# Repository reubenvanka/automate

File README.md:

# Auto Mate

Auto Mate is the working product repository for a smart-room controller. The current confirmed intent is coordinated control of lighting and fans, including brightness and color-temperature control, environmental sensing, Home Assistant integration, and a local/custom web interface.

## Current status

This repository contains the product foundation only. No GPIO assignments, controller model, electrical schematic, PCB, enclosure, or production safety decisions have been approved yet.

## Repository boundaries

- `SPECIFICATIONS.md` — source of truth.
- `firmware/esphome/` — future ESPHome product configuration and modules.
- `hardware/kicad/` — future KiCad projects and review artifacts.
- `tests/` — firmware, integration, UX, and hardware-review evidence.
- `docs/` — architecture, AI context, gates, traceability, and release evidence.
- `releases/` — approved release notes and artifacts.
- `backups/` — local working backups; not public release artifacts.

## Safety and review boundary

AI may prepare candidate firmware, schematics, netlists, PCB outlines, placement, and validation reports. A human must approve final GPIO mappings, electrical connections, component choices, load switching, placement, routing, safety behavior, and release.

## Security

Never commit Wi-Fi credentials, Home Assistant tokens, API keys, customer data, or private commercial information. Keep secrets outside Git and use documented configuration templates.

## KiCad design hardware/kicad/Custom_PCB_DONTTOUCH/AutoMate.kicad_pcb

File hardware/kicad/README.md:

# Auto Mate KiCad Hardware

This directory is reserved for KiCad projects, symbol/footprint libraries, netlists, ERC/DRC reports, and human review artifacts.

No schematic or PCB is manufacturing-ready until the hardware architecture is approved and the required human review is recorded.

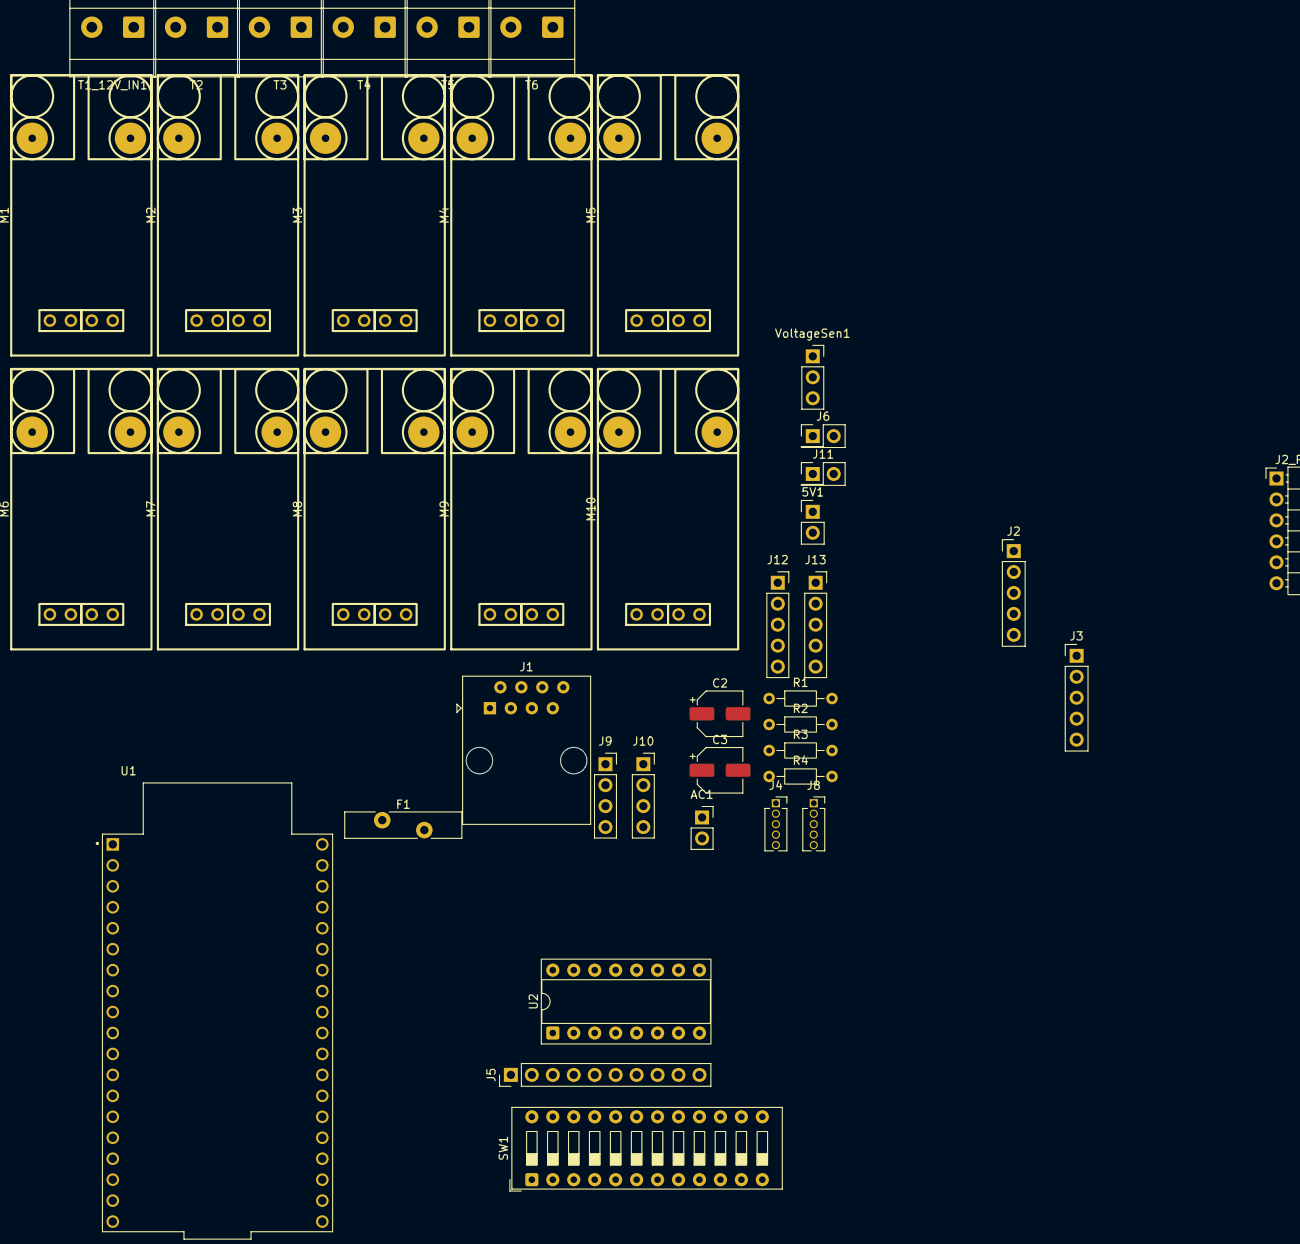
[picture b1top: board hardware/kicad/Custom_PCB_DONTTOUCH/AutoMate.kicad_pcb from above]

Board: 8 copper layers, 42 parts (0 on the bottom side), 24 nets, no tracks yet.

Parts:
5V1: GND; PinHeader_1x02_P2.54mm_Vertical
AC1: PinSocket_1x02_P2.54mm_Vertical
C2: 100nF; CP_Elec_5x3.9
C3: 470uf; CP_Elec_5x3.9
F1: Polyfuse; Fuse_Bourns_MF-RHT700
J1: 8P8C; RJ45_Amphenol_54602-x08_Horizontal
J2: SDA; PinHeader_1x05_P2.54mm_Vertical
J2_PCA9685: PCA9685; PinHeader_1x06_P2.54mm_Horizontal
J3: SCL; PinHeader_1x05_P2.54mm_Vertical
J4: +5V; PinSocket_1x05_P1.27mm_Vertical
J5: Relay; PinHeader_1x10_P2.54mm_Vertical
J6: tx rx; PinHeader_2x01_P2.54mm_Vertical
J8: GND; PinSocket_1x05_P1.27mm_Vertical
J9: ZMPT; PinSocket_1x04_P2.54mm_Vertical
J10: Sensors all; PinSocket_1x04_P2.54mm_Vertical
J11: Door Sensor; PinHeader_2x01_P2.54mm_Vertical
J12: a; PinSocket_1x05_P2.54mm_Vertical
J13: Rst-boot-led-ws2812b-3.3v; PinSocket_1x05_P2.54mm_Vertical
M1, M2, M3, M4, M5, M6, M7, M8, M9, M10: D4184 Module Custom Updated
R1, R3: 4.7k Pull-up SDA/SCL; R_Axial_DIN0204_L3.6mm_D1.6mm_P7.62mm_Horizontal
R2: 1k Ohm; R_Axial_DIN0204_L3.6mm_D1.6mm_P7.62mm_Horizontal
R4: 10k Pull-Down; R_Axial_DIN0204_L3.6mm_D1.6mm_P7.62mm_Horizontal
SW1: SW_DIP_x12; SW_DIP_SPSTx12_Slide_9.78x32.66mm_W7.62mm_P2.54mm
T1_12V_IN1, T2, T3, T4, T5, T6: Screw_Terminal_01x02; TerminalBlock_Phoenix_MKDS-3-2-5.08_1x02_P5.08mm_Horizontal
U1: ESP32-DEVKITC; MODULE_ESP32-DEVKITC
U2: 74HC595; DIP-16_W7.62mm_Socket
VoltageSen1: PinSocket_1x03_P2.54mm_Vertical

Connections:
04 PWM/Relay-WS2812b: J1.3, J13.2, R4.1
16 PWM/Relay/rx2: J1.6, J6.2, R2.2
17 PWM/Relay/tx2: J1.5, J6.1
21 SDA: J1.1, J2.1, J2.2, J2.3, J2.4, J2.5, R3.1
22 SCL: J1.8, J3.1, J3.2, J3.3, J3.4, J3.5, R1.1
34 IP_ONLY: J9.2, J10.3
35 IP_ONLY: J10.4, VoltageSen1.2
36 IP_ONLY: J10.1, J11.2
+3.3V: J1.7, J13.1, U1.1 (3V3)
+5V: AC1.1, C2.2, C3.2, F1.1, J1.4, J4.1, J4.2, J4.3, J4.4, J4.5, J5.10, J9.1, R1.2, R3.2, R4.2, VoltageSen1.1
GND: 5V1.2 (-), AC1.2, C2.1, C3.1, J1.2, J2_PCA9685.1, J5.1, J8.1, J8.2, J8.3, J8.4, J8.5, J9.3, J9.4, J11.1, J12.5, M1.4 (GND), M2.4 (GND), M3.4 (GND_4), M4.4 (GND_4), M5.4 (GND_4), M6.4 (GND_4), M7.4 (GND_4), M8.4 (GND_4), M9.4 (GND_4), M10.4 (GND_4), U1.38 (GND3), VoltageSen1.3
unnamed: 5V1.1 (+), F1.2
unnamed: J5.2, SW1.24, U2.15 (QA)
unnamed: J5.3, SW1.23, U2.1 (QB)
unnamed: J5.4, SW1.22, U2.2 (QC)
unnamed: J5.5, SW1.21, U2.3 (QD)
unnamed: J5.6, SW1.20, U2.4 (QE)
unnamed: J5.7, SW1.19, U2.5 (QF)
unnamed: J5.8, SW1.18, U2.6 (QG)
unnamed: J5.9, SW1.17, U2.7 (QH)
unnamed: SW1.1, SW1.2, SW1.3, SW1.4, SW1.5, SW1.6, SW1.7, SW1.8, SW1.9, SW1.10, SW1.11, SW1.12
PCA9685_OE (with 10kΩ pull-up to 3.3V): J2_PCA9685.2, U1.25 (IO0)
PWM_CEILING_COLD: M2.1 (PWM), U1.34 (RXD0)
PWM_CEILING_WARM: M1.1 (PWM), U1.35 (TXD0)

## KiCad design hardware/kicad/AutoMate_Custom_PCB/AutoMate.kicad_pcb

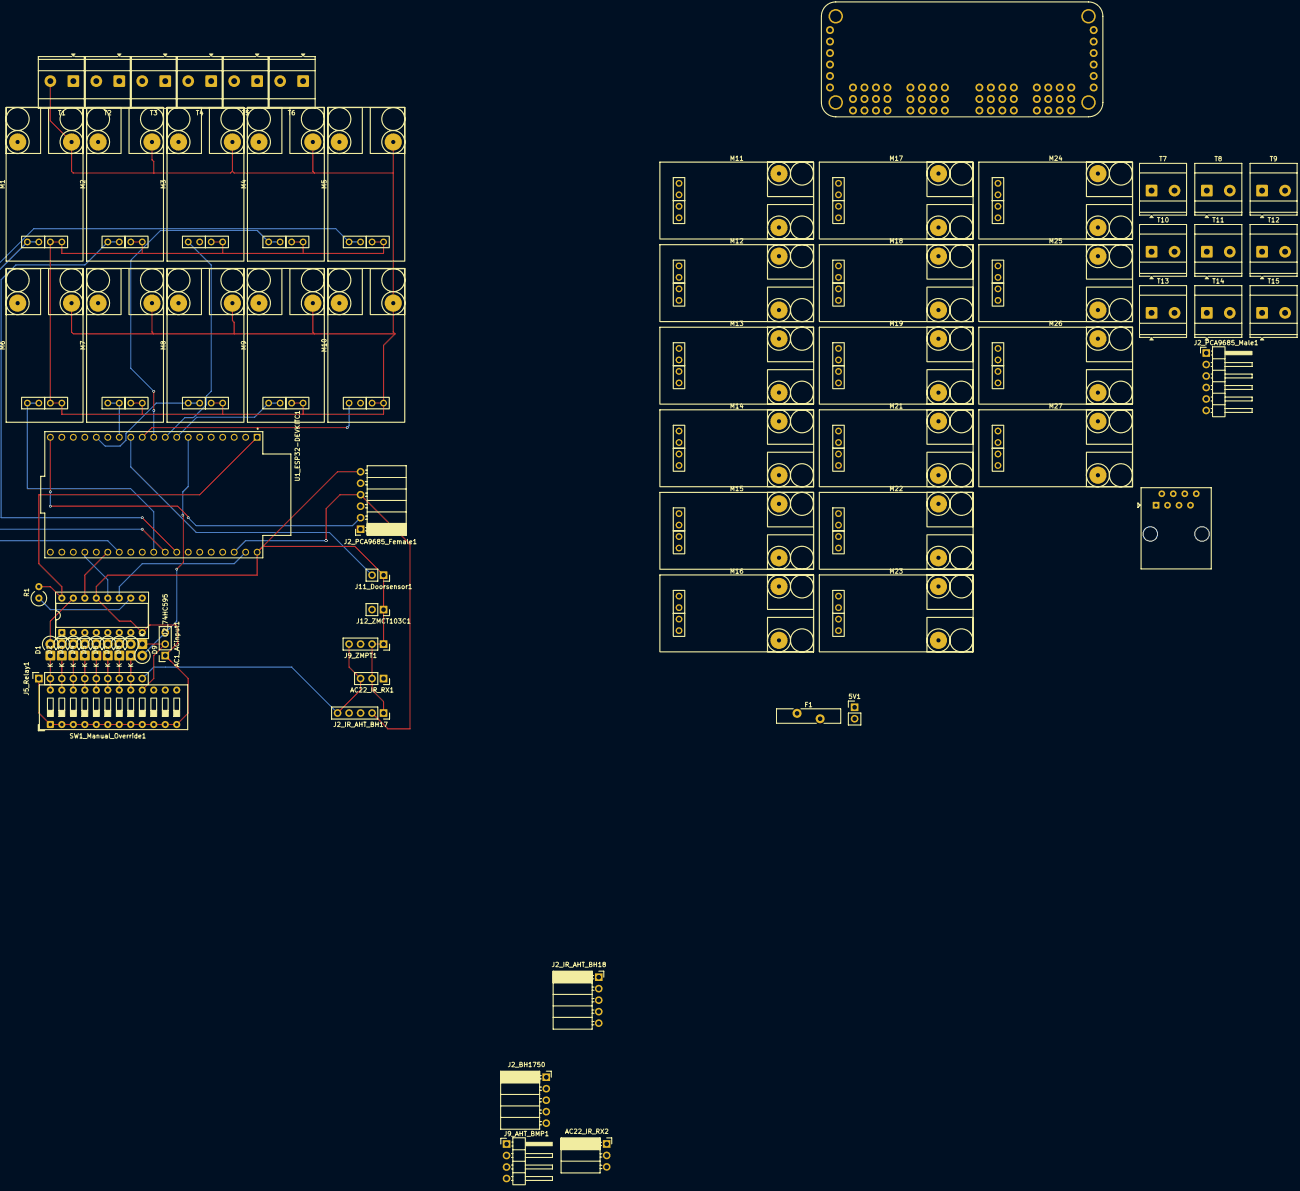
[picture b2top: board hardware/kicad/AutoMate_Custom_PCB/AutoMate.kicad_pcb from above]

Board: 8 copper layers, 71 parts (0 on the bottom side), 85 nets.

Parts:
5V1: GND; PinHeader_1x02_P2.54mm_Vertical
AC1_ACinput1, AC22_IR_RX1: Conn_01x03_Socket; PinSocket_1x03_P2.54mm_Vertical
AC22_IR_RX2: Conn_01x03_Socket; PinSocket_1x03_P2.54mm_Horizontal
D1, D2, D3, D4, D5, D6, D7, D8, D9: 1N5817; D_DO-41_SOD81_P2.54mm_Vertical_CathodeUp
F1: Polyfuse; Fuse_Bourns_MF-RHT700
J1: 8P8C; RJ45_Amphenol_54602-x08_Horizontal
J2_BH1750, J2_IR_AHT_BH18: Conn_01x05_Socket; PinSocket_1x05_P2.54mm_Horizontal
J2_IR_AHT_BH17: Conn_01x05_Socket; PinSocket_1x05_P2.54mm_Vertical
J2_PCA9685_Female1: PCA9685; PinSocket_1x06_P2.54mm_Horizontal
J2_PCA9685_Male1: PCA9685; PinHeader_1x06_P2.54mm_Horizontal
J5_Relay1: Relay; PinSocket_1x10_P2.54mm_Vertical
J9_AHT_BMP1: Conn_01x04_Socket; PinHeader_1x04_P2.54mm_Horizontal
J9_ZMPT1: Conn_01x04_Socket; PinSocket_1x04_P2.54mm_Vertical
J11_Doorsensor1, J12_ZMCT103C1: Conn_01x02_Socket; PinSocket_1x02_P2.54mm_Vertical
M1, M2, M3, M4, M5, M6, M7, M8, M9, M10, M11, M12, M13, M14, M15, M16, M17, M18, M19, M21, M22, M23, M24, M25, M26, M27: D4184 Module Custom Updated
R1: 10k; R_Axial_DIN0309_L9.0mm_D3.2mm_P2.54mm_Vertical
SW1_Manual_Override1: SW_DIP_x12; SW_DIP_SPSTx12_Slide_9.78x32.66mm_W7.62mm_P2.54mm
T1, T2, T3, T4, T5, T6, T7: Screw_Terminal_01x02; TerminalBlock_Phoenix_MKDS-3-2-5.08_1x02_P5.08mm_Horizontal
T8, T9, T10, T11, T12, T13, T14, T15: ST01x02; TerminalBlock_Phoenix_MKDS-3-2-5.08_1x02_P5.08mm_Horizontal
U1: 815; MODULE_815_pca9685
U1_ESP32-DEVKITC1: ESP32-DEVKITC; MODULE_ESP32-DEVKITC
U2_74HC595: 74HC595; DIP-16_W7.62mm_Socket

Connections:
30A_JN: AC1_ACinput1.3, D9.1, SW1_Manual_Override1.16
+3.3V: J1.7, R1.2, U1_ESP32-DEVKITC1.1 (3V3), U2_74HC595.16 (VCC)
+5V: AC1_ACinput1.1, AC22_IR_RX1.3, AC22_IR_RX2.3, F1.1, J1.4, J2_BH1750.5, J2_IR_AHT_BH17.5, J2_IR_AHT_BH18.5, J2_PCA9685_Female1.2, J2_PCA9685_Male1.5, J5_Relay1.10, J9_AHT_BMP1.1, J9_ZMPT1.4, U1.VCC_1 (VCC), U1.VCC_2 (VCC), U1_ESP32-DEVKITC1.19 (EXT_5V)
+12V: T1.1, T7.1
BACKUP_01: M26.1 (PWM), M26.2 (PWM), U1.14 (PWM_14)
BACKUP_02: M27.1 (PWM), M27.2 (PWM), U1.15 (PWM_15)
BU1: M26.5 (Led), T15.1
BU2: M27.5 (Led), T15.2
CBL: M18.5 (Led), T11.2
CC: M2.5 (Led), T2.2
CEILING_COLD: M2.1 (PWM), M2.2 (PWM), U1_ESP32-DEVKITC1.31 (IO19)
CEILING_WARM: M1.1 (PWM), M1.2 (PWM), U1_ESP32-DEVKITC1.30 (IO18)
CSL: M19.5 (Led), T12.1
CUPBOARD_BOUNCE_LIGHT: M18.1 (PWM), M18.2 (PWM), U1.7 (PWM_7)
CUPBOARD_SPOT_LIGHT: M19.1 (PWM), M19.2 (PWM), U1.8 (PWM_8)
CW: M1.5 (Led), T2.1
D1C: M4.5 (Led), T3.2
D1W: M3.5 (Led), T3.1
D2C: M6.5 (Led), T4.2
D2W: M5.5 (Led), T4.1
DESK1_COLD: M4.1 (PWM), M4.2 (PWM), U1_ESP32-DEVKITC1.10 (IO26)
DESK1_WARM: M3.1 (PWM), M3.2 (PWM), U1_ESP32-DEVKITC1.9 (IO25)
DESK2_COLD: M6.1 (PWM), M6.2 (PWM), U1_ESP32-DEVKITC1.29 (IO5)
DESK2_WARM: M5.1 (PWM), M5.2 (PWM), U1_ESP32-DEVKITC1.26 (IO4)
DESK_LIGHT1: M12.1 (PWM), M12.2 (PWM), U1.1 (PWM_1)
DESK_LIGHT2: M16.1 (PWM), M16.2 (PWM), U1.5 (PWM_5)
DL1: M12.5 (Led), T8.2
DL2: M16.5 (Led), T10.2
DOOR_SENSOR: J11_Doorsensor1.2, U1_ESP32-DEVKITC1.12 (IO14)
DOOR_SPOT_LIGHT: M21.1 (PWM), M21.2 (PWM), U1.9 (PWM_9)
DSL: M21.5 (Led), T12.2
EF: M24.5 (Led), T14.1
EXHAUST_FANS: M24.1 (PWM), M24.2 (PWM), U1.12 (PWM_12)
GND: 5V1.2 (-), AC1_ACinput1.2, AC22_IR_RX1.2, AC22_IR_RX2.2, J1.2, J2_BH1750.1, J2_IR_AHT_BH17.1, J2_IR_AHT_BH18.1, J2_PCA9685_Female1.6, J2_PCA9685_Male1.1, J5_Relay1.1, J9_AHT_BMP1.3, J9_ZMPT1.1, J9_ZMPT1.2, J11_Doorsensor1.1, J12_ZMCT103C1.1, M1.3 (GND), M1.4 (GND), M1.6 (Gnd), M2.3 (GND), M2.4 (GND), M2.6 (Gnd), M3.3 (GND), M3.4 (GND), M3.6 (Gnd), M4.3 (GND), M4.4 (GND), M4.6 (Gnd), M5.3 (GND), M5.4 (GND), M5.6 (Gnd), M6.3 (GND), M6.4 (GND), M6.6 (Gnd), M7.3 (GND), M7.4 (GND), M7.6 (Gnd), M8.3 (GND), M8.4 (GND), M8.6 (Gnd), M9.3 (GND), M9.4 (GND), M9.6 (Gnd), M10.3 (GND), M10.4 (GND), M10.6 (Gnd), M11.3 (GND), M11.4 (GND), M11.6 (Gnd), M12.3 (GND), M12.4 (GND), M12.6 (Gnd), M13.3 (GND), M13.4 (GND), M13.6 (Gnd), M14.3 (GND), M14.4 (GND), M14.6 (Gnd), M15.3 (GND), M15.4 (GND), M15.6 (Gnd), M16.3 (GND), M16.4 (GND), M16.6 (Gnd), M17.3 (GND), M17.4 (GND), M17.6 (Gnd), M18.3 (GND), M18.4 (GND), M18.6 (Gnd), M19.3 (GND), M19.4 (GND), M19.6 (Gnd), M21.3 (GND), M21.4 (GND), M21.6 (Gnd), M22.3 (GND), M22.4 (GND), M22.6 (Gnd), M23.3 (GND), M23.4 (GND), M23.6 (Gnd), M24.3 (GND), M24.4 (GND), M24.6 (Gnd), M25.3 (GND), M25.4 (GND), M25.6 (Gnd), M26.3 (GND), M26.4 (GND), M26.6 (Gnd), M27.3 (GND), M27.4 (GND), M27.6 (Gnd), SW1_Manual_Override1.1, SW1_Manual_Override1.2, SW1_Manual_Override1.3, SW1_Manual_Override1.4, SW1_Manual_Override1.5, SW1_Manual_Override1.6, SW1_Manual_Override1.7, SW1_Manual_Override1.8, SW1_Manual_Override1.9, SW1_Manual_Override1.10, SW1_Manual_Override1.11, SW1_Manual_Override1.12, T1.2, T7.2, U1.GND_1 (GND), U1.GND_2 (GND), U1.GND_3 (GND), U1.GND_4 (GND), U1.GND_5 (GND), U1.GND_6 (GND), U1.GND_7 (GND), U1.GND_8 (GND), U1.GND_9 (GND), U1.GND_10 (GND), U1.GND_11 (GND), U1.GND_12 (GND), U1.GND_13 (GND), U1.GND_14 (GND), U1.GND_15 (GND), U1.GND_16 (GND), U1.GND_17 (GND), U1.GND_18 (GND), U1_ESP32-DEVKITC1.38 (GND3), U2_74HC595.8 (GND), U2_74HC595.13 (~OE)
I2C_SCL: J2_BH1750.4, J2_IR_AHT_BH17.2, J2_IR_AHT_BH18.2, J2_PCA9685_Female1.4, J2_PCA9685_Male1.3, J9_AHT_BMP1.4, U1.SCL_1 (SCL), U1.SCL_2 (SCL), U1_ESP32-DEVKITC1.36 (IO22)
I2C_SDA: J2_BH1750.3, J2_IR_AHT_BH17.3, J2_IR_AHT_BH18.3, J2_PCA9685_Female1.3, J2_PCA9685_Male1.4, J9_AHT_BMP1.2, U1.SDA_1 (SDA), U1.SDA_2 (SDA), U1_ESP32-DEVKITC1.33 (IO21)
IR_RX: AC22_IR_RX1.1, AC22_IR_RX2.1, J2_IR_AHT_BH17.4, J2_IR_AHT_BH18.4, U1_ESP32-DEVKITC1.4 (SENSOR_VN)
M1B: M11.5 (Led), T8.1
M2B: M15.5 (Led), T10.1
M3B: M22.5 (Led), T13.1
M4B: M23.5 (Led), T13.2
MONITOR1_BACKLIGHT: M11.1 (PWM), M11.2 (PWM), U1.0 (PWM_0)
MONITOR2_BACKLIGHT: M15.1 (PWM), M15.2 (PWM), U1.4 (PWM_4)
MONITOR3_BACKLIGHT: M22.1 (PWM), M22.2 (PWM), U1.10 (PWM_10)
MONITOR4_BACKLIGHT: M23.1 (PWM), M23.2 (PWM), U1.11 (PWM_11)
unnamed: 5V1.1 (+), F1.2
unnamed: D1.1, J5_Relay1.2, SW1_Manual_Override1.24
unnamed: D2.1, J5_Relay1.3, SW1_Manual_Override1.23
unnamed: D3.1, J5_Relay1.4, SW1_Manual_Override1.22
unnamed: D4.1, J5_Relay1.5, SW1_Manual_Override1.21
unnamed: D5.1, J5_Relay1.6, SW1_Manual_Override1.20
unnamed: D6.1, J5_Relay1.7, SW1_Manual_Override1.19
unnamed: D7.1, J5_Relay1.8, SW1_Manual_Override1.18
unnamed: D8.1, J5_Relay1.9, SW1_Manual_Override1.17
unnamed: D1.2, U2_74HC595.15 (QA)
unnamed: D2.2, U2_74HC595.1 (QB)
unnamed: D3.2, U2_74HC595.2 (QC)
unnamed: D4.2, U2_74HC595.3 (QD)
unnamed: D5.2, U2_74HC595.4 (QE)
unnamed: D6.2, U2_74HC595.5 (QF)
unnamed: D7.2, U2_74HC595.6 (QG)
unnamed: D8.2, U2_74HC595.7 (QH)
unnamed: R1.1, U2_74HC595.10 (~SRCLR)
PHOTO_SPOT_LIGHT: M7.1 (PWM), M7.2 (PWM), U1_ESP32-DEVKITC1.13 (IO12)
PSL: M8.5 (Led), T5.2
RCLK: U1_ESP32-DEVKITC1.23 (IO15), U2_74HC595.12 (RCLK)
RELAY_30A: D9.2, U1_ESP32-DEVKITC1.7 (IO32)
SER: U1_ESP32-DEVKITC1.25 (IO0), U2_74HC595.14 (SER)
SHELF_LIGHT1: M14.1 (PWM), M14.2 (PWM), U1.3 (PWM_3)
SHELF_LIGHT2: M17.1 (PWM), M17.2 (PWM), U1.6 (PWM_6)
SHL1: M14.5 (Led), T9.2
SHL2: M17.5 (Led), T11.1
SRCLK: U1_ESP32-DEVKITC1.37 (IO23), U2_74HC595.11 (SRCLK)
TABLE_LIGHT: M13.1 (PWM), M13.2 (PWM), U1.2 (PWM_2)
TAL: M25.5 (Led), T14.2
TBLL: M13.5 (Led), T9.1
TERRACE_AMBIENT_LIGHT: M25.1 (PWM), M25.2 (PWM), U1.13 (PWM_13)
TERRACE_LIGHT: M10.1 (PWM), M10.2 (PWM), U1_ESP32-DEVKITC1.11 (IO27)
TL: M10.5 (Led), T6.2
WALL_BOUNCE_LIGHT: M8.1 (PWM), M8.2 (PWM), U1_ESP32-DEVKITC1.15 (IO13)
WASHROOM_LIGHT: M9.1 (PWM), M9.2 (PWM), U1_ESP32-DEVKITC1.8 (IO33)
WBL: M7.5 (Led), T5.1
WL: M9.5 (Led), T6.1
ZMCT103C_CURRENT: J12_ZMCT103C1.2, U1_ESP32-DEVKITC1.5 (IO34)
ZMPT101B_VOLTAGE: J9_ZMPT1.3, U1_ESP32-DEVKITC1.6 (IO35)

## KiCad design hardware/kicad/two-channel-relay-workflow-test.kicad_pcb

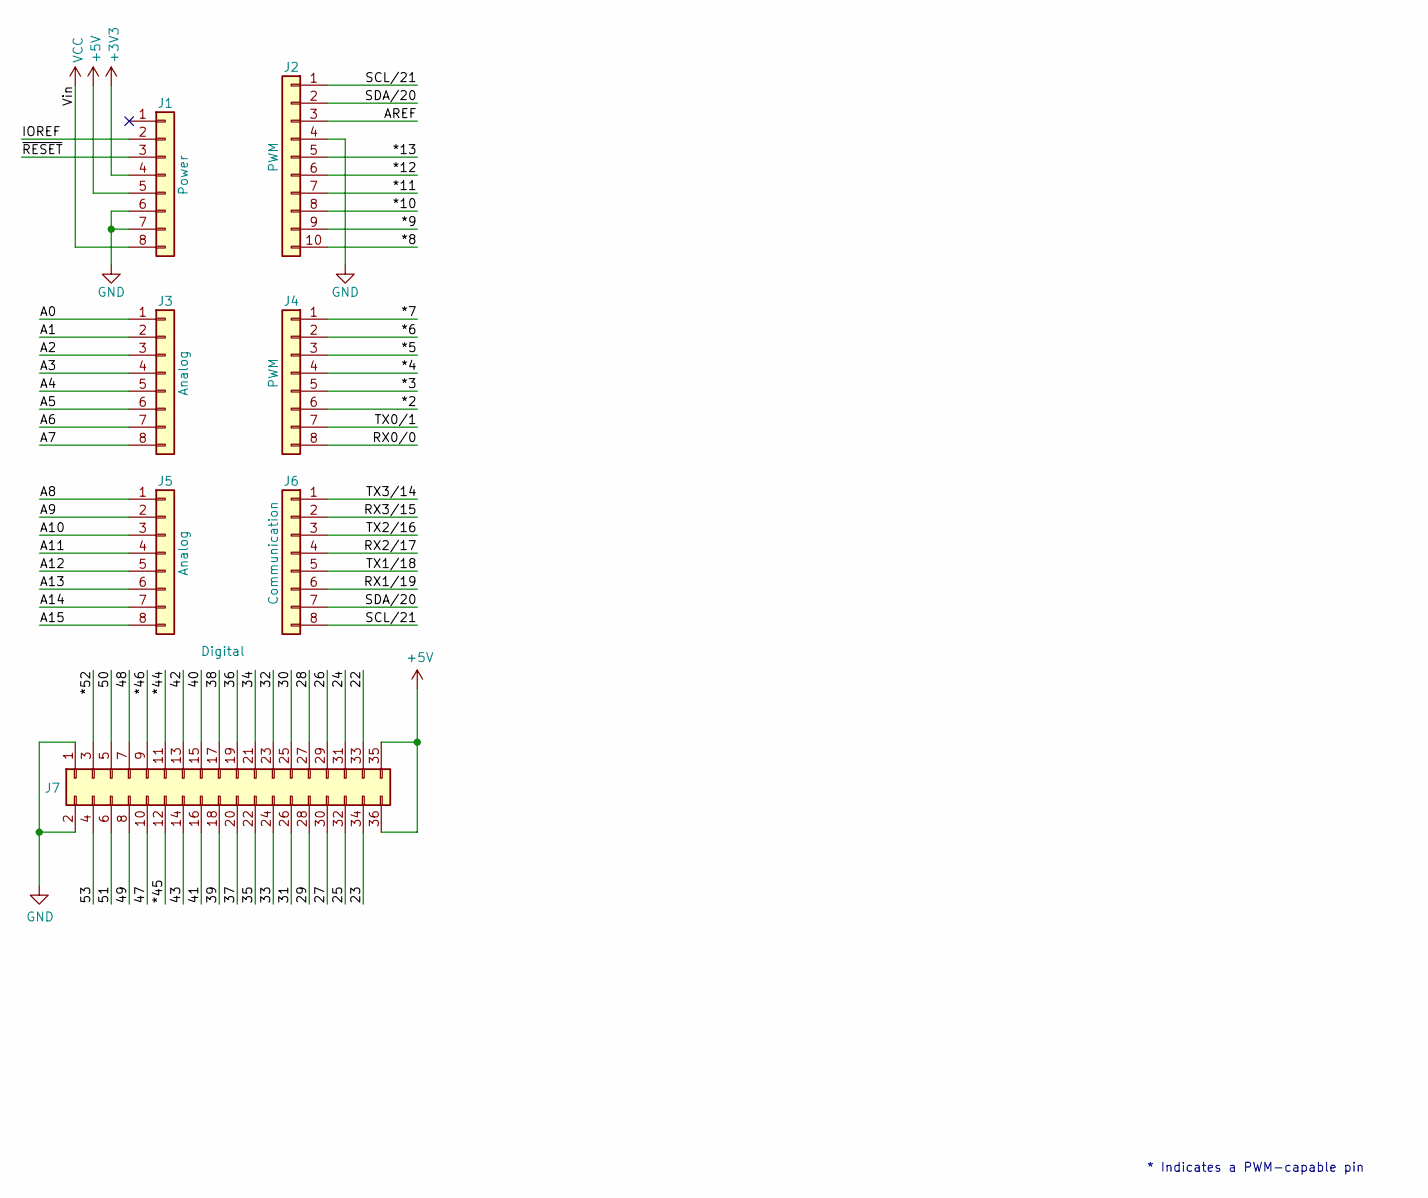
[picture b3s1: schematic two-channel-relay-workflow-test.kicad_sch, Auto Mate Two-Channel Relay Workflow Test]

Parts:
J1: Power; PinSocket_1x08_P2.54mm_Vertical
J2: PWM; PinSocket_1x10_P2.54mm_Vertical
J3, J5: Analog; PinSocket_1x08_P2.54mm_Vertical
J4: PWM; PinSocket_1x08_P2.54mm_Vertical
J6: Communication; PinSocket_1x08_P2.54mm_Vertical
J7: Digital; PinSocket_2x18_P2.54mm_Vertical

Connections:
+3V3: J1.4
+5V: J1.5, J7.35, J7.36
/22: J7.33
/23: J7.34
/24: J7.31
/25: J7.32
/26: J7.29
/27: J7.30
/28: J7.27
/29: J7.28
/30: J7.25
/31: J7.26
/32: J7.23
/33: J7.24
/34: J7.21
/35: J7.22
/36: J7.19
/37: J7.20
/38: J7.17
/39: J7.18
/40: J7.15
/41: J7.16
/42: J7.13
/43: J7.14
/47: J7.10
/48: J7.7
/49: J7.8
/50: J7.5
/51: J7.6
/53: J7.4
/*2: J4.6
/*3: J4.5
/*4: J4.4
/*5: J4.3
/*6: J4.2
/*7: J4.1
/*8: J2.10
/*9: J2.9
/*10: J2.8
/*11: J2.7
/*12: J2.6
/*13: J2.5
/*44: J7.11
/*45: J7.12
/*46: J7.9
/*52: J7.3
/A0: J3.1
/A1: J3.2
/A2: J3.3
/A3: J3.4
/A4: J3.5
/A5: J3.6
/A6: J3.7
/A7: J3.8
/A8: J5.1
/A9: J5.2
/A10: J5.3
/A11: J5.4
/A12: J5.5
/A13: J5.6
/A14: J5.7
/A15: J5.8
/AREF: J2.3
/IOREF: J1.2
/RX0/0: J4.8
/RX1/19: J6.6
/RX2/17: J6.4
/RX3/15: J6.2
/SCL/21: J2.1, J6.8
/SDA/20: J2.2, J6.7
/TX0/1: J4.7
/TX1/18: J6.5
/TX2/16: J6.3
/TX3/14: J6.1
/~RESET: J1.3
GND: J1.6, J1.7, J2.4, J7.1, J7.2
VCC: J1.8

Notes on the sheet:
* Indicates a PWM-capable pin

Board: 2 copper layers, 13 parts (0 on the bottom side), 4 nets, no tracks yet.

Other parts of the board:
MH1, MH2, MH3, MH4, MH5, MH6: MountingHole_3.2mm

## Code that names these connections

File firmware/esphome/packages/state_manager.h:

#pragma once

#include "esphome/core/component.h"
#include "esphome/core/preferences.h"
#include <vector>
#include <cstdint>
#include <cstring>

namespace esphome {
namespace automate {

enum RelayId : uint8_t {
  RELAY_FAN = 0,
  RELAY_CEILING = 1,
  RELAY_12V = 2,
  RELAY_STABILIZER = 3,
  RELAY_DESK1 = 4,
  RELAY_DESK2 = 5,
  RELAY_DESK3 = 6,
  RELAY_AC = 7,
  RELAY_30A = 8,
  RELAY_COUNT = 9
};

enum PwmId : uint8_t {
  PWM_CEILING_WARM = 0,
  PWM_CEILING_COLD = 1,
  PWM_DESK1_WARM = 2,
  PWM_DESK1_COLD = 3,
  PWM_DESK2_WARM = 4,
  PWM_DESK2_COLD = 5,
  PWM_MONITOR1_BACKLIGHT = 6,
  PWM_DESK_LIGHT1 = 7,
  PWM_TABLE_LIGHT = 8,
  PWM_SHELF_LIGHT1 = 9,
  PWM_MONITOR2_BACKLIGHT = 10,
  PWM_DESK_LIGHT2 = 11,
  PWM_SHELF_LIGHT2 = 12,
  PWM_WALL_BOUNCE = 13,
  PWM_PHOTO_SPOT = 14,
  PWM_CUPBOARD_BOUNCE = 15,
  PWM_CUPBOARD_SPOT = 16,
  PWM_DOOR_SPOT = 17,
  PWM_MONITOR_LIGHT3 = 18,
  PWM_MONITOR_LIGHT4 = 19,
  PWM_EXHAUST_FANS = 20,
  PWM_WASHROOM_LIGHT = 21,
  PWM_TERRACE_LIGHT = 22,
  PWM_TERRACE_AMBIENT = 23,
  PWM_COUNT = 24
};

enum MaintenanceMode : uint8_t {
  MAINTENANCE_AUTO = 0,
  MAINTENANCE_FORCE_ON = 1,
  MAINTENANCE_FORCE_OFF = 2
};

constexpr size_t MAX_SCENES = 10;
constexpr size_t SCENE_NAME_MAX_LEN = 32;
constexpr uint32_t SCENE_STORAGE_VERSION = 1;
constexpr uint32_t STATE_STORAGE_VERSION = 1;

struct SceneData {
  uint32_t version;
  uint32_t crc32;
  char name[SCENE_NAME_MAX_LEN];
  float pwm_values[PWM_COUNT];
  bool relay_values[RELAY_COUNT];
  uint32_t timestamp;
};

struct DesiredState {
  uint32_t version;
  uint32_t crc32;
  float pwm_values[PWM_COUNT];
  bool relay_values[RELAY_COUNT];
  MaintenanceMode maint_modes[RELAY_COUNT];
  uint32_t timestamp;
};

class StateManager : public Component, public PreferenceObject {
 public:
  StateManager() = default;

  void setup() override;
  void dump_config() override;

  void set_desired_pwm(PwmId id, float value);
  void set_desired_relay(RelayId id, bool value);
  float get_desired_pwm(PwmId id) const;
  bool get_desired_relay(RelayId id) const;
  MaintenanceMode get_maintenance_mode(RelayId id) const;
  void set_maintenance_mode(RelayId id, MaintenanceMode mode);

  bool check_interlocks(RelayId id, bool value);
  void update_dependency_relays();

  void save_scene(uint8_t scene_id, const char* name);
  bool load_scene(uint8_t scene_id);
  void delete_scene(uint8_t scene_id);

  bool restore_valid_state();
  bool validate_state_safety();
  void set_all_outputs_off();
  void update_effective_outputs();

  void save_desired_state();
  bool load_desired_state();
  void load_scenes();

  uint32_t calculate_crc32(const void* data, size_t length);

  void restore_valid_state_service();
  void save_scene_service(uint8_t scene_id, const std::string& name);
  void load_scene_service(uint8_t scene_id);
  void delete_scene_service(uint8_t scene_id);

  std::string get_state_summary();

 private:
  DesiredState desired_state_;
  MaintenanceMode maint_modes_[RELAY_COUNT];
  bool initialized_ = false;
};

}  // namespace automate
}  // namespace esphome

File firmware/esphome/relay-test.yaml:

# AutoMate — 74HC595 relay bench test (standalone)
# -----------------------------------------------------
# Purpose: verify ONLY the 74HC595 shift register + 8-ch relay board.
# Does NOT use WiFi / API / packages — run over USB serial.
#
#   Flash:  cd firmware/esphome && esphome run relay-test.yaml
#   Watch:  open the serial logger (`esphome logs relay-test.yaml`)
#           Each channel Q0..Q7 should energise in turn for ~1s
#           (you should hear/see 8 distinct relay clicks + the on-board
#           status LED blink on each).
#
# Wiring (must match boards):
#   74HC595  SER   -> GPIO0
#   74HC595  SRCLK -> GPIO23
#   74HC595  RCLK  -> GPIO15
#   (SRCLR -> +3.3V via 10k, OE -> GND, VCC -> 3.3V, GND -> GND)
#   74HC595 Q0..Q7 -> Relay Module IN1..IN8 (active-LOW, direct connection)
#
# Relays are wired as `inverted: true` matching active-LOW module:
#   switch ON -> register bit 0 -> 74HC595 Q LOW -> Relay ON
#   switch OFF -> register bit 1 -> 74HC595 Q HIGH -> Relay OFF

esphome:
  name: relay-test
  friendly_name: Relay Test
  on_boot:
    then:
      - logger.log: "74HC595 relay test starting (Q0..Q7)..."
      - delay: 500ms
      - output.turn_on: relay_0
      - script.execute: blink_status
      - logger.log: "Q0 ON — if no click, shift register is not latching"
      - delay: 1000ms
      - output.turn_off: relay_0
      - delay: 300ms
      - output.turn_on: relay_1
      - script.execute: blink_status
      - logger.log: "Q1 ON"
      - delay: 1000ms
      - output.turn_off: relay_1
      - delay: 300ms
      - output.turn_on: relay_2
      - script.execute: blink_status
      - logger.log: "Q2 ON"
      - delay: 1000ms
      - output.turn_off: relay_2
      - delay: 300ms
      - output.turn_on: relay_3
      - script.execute: blink_status
      - logger.log: "Q3 ON"
      - delay: 1000ms
      - output.turn_off: relay_3
      - delay: 300ms
      - output.turn_on: relay_4
      - script.execute: blink_status
      - logger.log: "Q4 ON"
      - delay: 1000ms
      - output.turn_off: relay_4
      - delay: 300ms
      - output.turn_on: relay_5
      - script.execute: blink_status
      - logger.log: "Q5 ON"
      - delay: 1000ms
      - output.turn_off: relay_5
      - delay: 300ms
      - output.turn_on: relay_6
      - script.execute: blink_status
      - logger.log: "Q6 ON"
      - delay: 1000ms
      - output.turn_off: relay_6
      - delay: 300ms
      - output.turn_on: relay_7
      - script.execute: blink_status
      - logger.log: "Q7 ON"
      - delay: 1000ms
      - output.turn_off: relay_7
      - delay: 300ms
      - logger.log: "74HC595 relay test complete. All 8 channels exercised."

esp32:
  board: esp32dev
  framework:
    type: esp-idf

logger:
  baud_rate: 115200

# 74HC595 on the verified pins
sn74hc595:
  - id: sr_relays
    data_pin: GPIO0
    clock_pin: GPIO23
    latch_pin: GPIO15
    sr_count: 1

# On-board status LED (blinks per channel so you can follow along)
output:
  - platform: gpio
    id: status_led
    pin:
      number: GPIO2
      inverted: false   # active-HIGH on this DevKit

# 8 relay outputs -> Q0..Q7 (all active-LOW, hence inverted: true)
  - platform: gpio
    id: relay_0
    pin: { sn74hc595: sr_relays, number: 0, inverted: true }
  - platform: gpio
    id: relay_1
    pin: { sn74hc595: sr_relays, number: 1, inverted: true }
  - platform: gpio
    id: relay_2
    pin: { sn74hc595: sr_relays, number: 2, inverted: true }
  - platform: gpio
    id: relay_3
    pin: { sn74hc595: sr_relays, number: 3, inverted: true }
  - platform: gpio
    id: relay_4
    pin: { sn74hc595: sr_relays, number: 4, inverted: true }
  - platform: gpio
    id: relay_5
    pin: { sn74hc595: sr_relays, number: 5, inverted: true }
  - platform: gpio
    id: relay_6
    pin: { sn74hc595: sr_relays, number: 6, inverted: true }
  - platform: gpio
    id: relay_7
    pin: { sn74hc595: sr_relays, number: 7, inverted: true }

# Blink helper
script:
  - id: blink_status
    then:
      - output.turn_on: status_led
      - delay: 100ms
      - output.turn_off: status_led
